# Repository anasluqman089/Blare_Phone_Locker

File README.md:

# Blare_Phone_Locker

I have created a fusion between an alarm and a phone locker

The alarm have three button.

1. Switching mode

2. Action

3. Action

The main purpose of this product is to help other teenagers to stop doomscrolling and instead locked in.
I too have trouble with studying due to me addicted to my phone

There are two modes 

1. Clock

The user can set  the alarm by clicking the second button and change the alarm by pressing the third button
when pressed the third button the time will go up 30 minutes. the use can set the alarm by pressing the second button again

2. Phone Locker

The user can lock the phone by pressing the second button and can set how much time to lock by pressing the third button, it is the same as the clock it will add 30 minutes. User must put the phone in the compartment and presssed the second button again. The Locker uses hinge system.

# BOM
1x Seeed Studio XIAO ESP32-C3

3x Cherry MX Switches

1x SG90 servo

1x Buzzer

1x 220uf polarized capacitor

1x 2.25 inch TFT Display

# Schematic

# PCB

# Alarm Case

Case

Lid

# Locker Case

Compartment

lid

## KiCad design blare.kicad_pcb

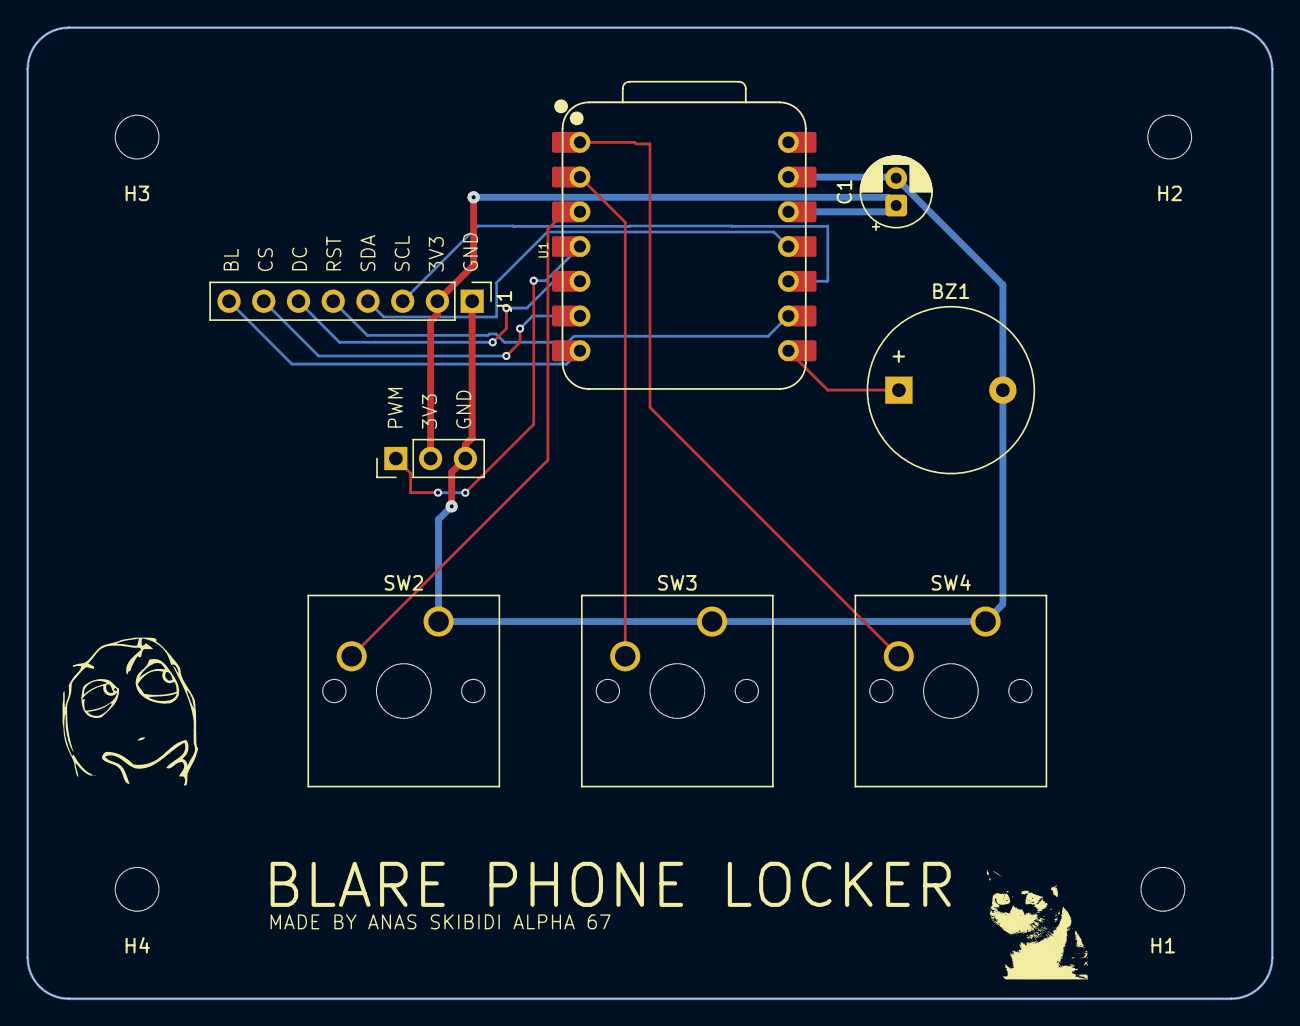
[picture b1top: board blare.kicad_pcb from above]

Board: 2 copper layers, 91.0 x 71.0 mm, 12 parts (0 on the bottom side), 13 nets.

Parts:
BZ1: Buzzer; Buzzer_12x9.5RM7.6
C1: C_Polarized_Small; CP_Radial_D5.0mm_P2.00mm
H1, H2, H3, H4: MountingHole; MountingHole_3.2mm_M3
J1: Conn_01x08_Pin; PinHeader_1x08_P2.54mm_Vertical
M1: Motor_Servo; PinHeader_1x03_P2.54mm_Vertical
SW2, SW3, SW4: SW_Push; SW_Cherry_MX_1.00u_PCB
U1: XIAO-ESP32-C3-SMD; XIAO-ESP32-C3-DIP

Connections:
+3.3V: C1.1, J1.2, M1.2 (+), U1.12 (3V3_OUT)
/BL: J1.8, U1.7 (D6)
/CS: J1.7, U1.6 (D5)
/DC: J1.6, U1.5 (D4)
/RST: J1.5, U1.9 (D8)
/SCL: J1.3, U1.10 (D9/BOOT)
/SDA: J1.4, U1.11 (D10)
GND: BZ1.2 (-), C1.2, J1.1, M1.3 (-), SW2.1, SW3.1, SW4.1, U1.13 (GND)
unnamed: BZ1.1 (+), U1.8 (D7)
unnamed: M1.1 (PWM), U1.4 (D3)
unnamed: SW4.2, U1.1 (D0)
unnamed: SW3.2, U1.2 (D1)
unnamed: SW2.2, U1.3 (D2)
